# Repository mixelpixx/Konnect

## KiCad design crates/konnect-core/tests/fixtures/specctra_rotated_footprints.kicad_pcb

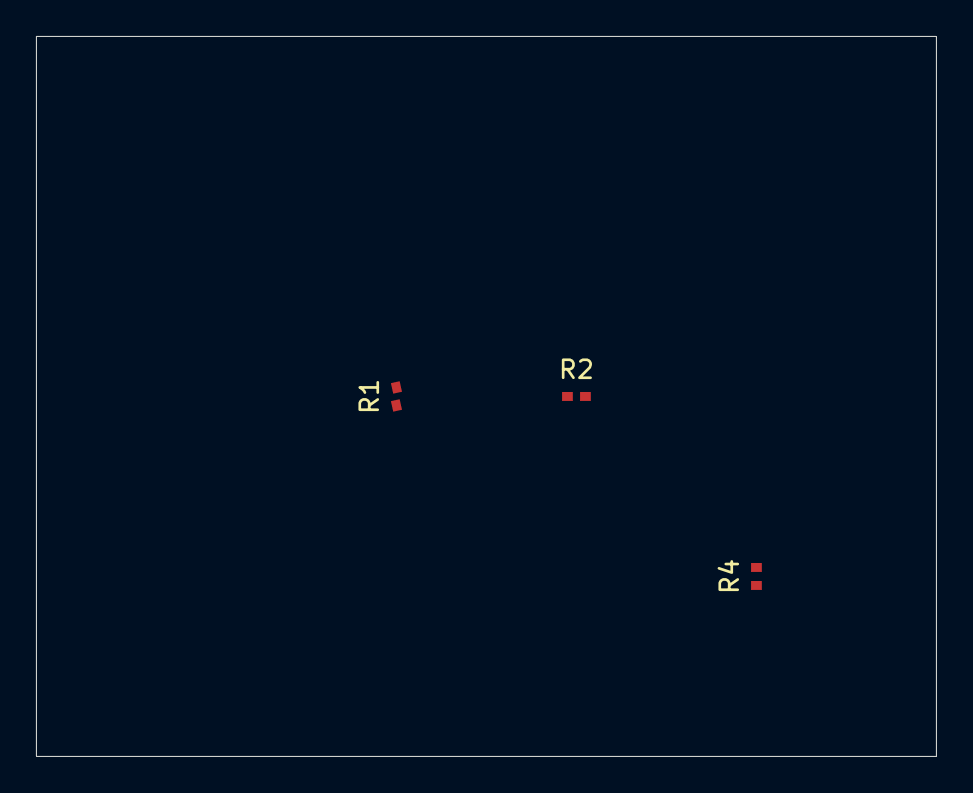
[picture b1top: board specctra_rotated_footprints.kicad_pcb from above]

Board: 2 copper layers, 50.0 x 40.0 mm, 3 parts (0 on the bottom side), 2 nets, no tracks yet.

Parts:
R1: 10k; R_0402
R2, R4: 4.7k; R_0402

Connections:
GND: R1.2, R2.1, R4.1
VCC: R1.1, R2.2, R4.2
